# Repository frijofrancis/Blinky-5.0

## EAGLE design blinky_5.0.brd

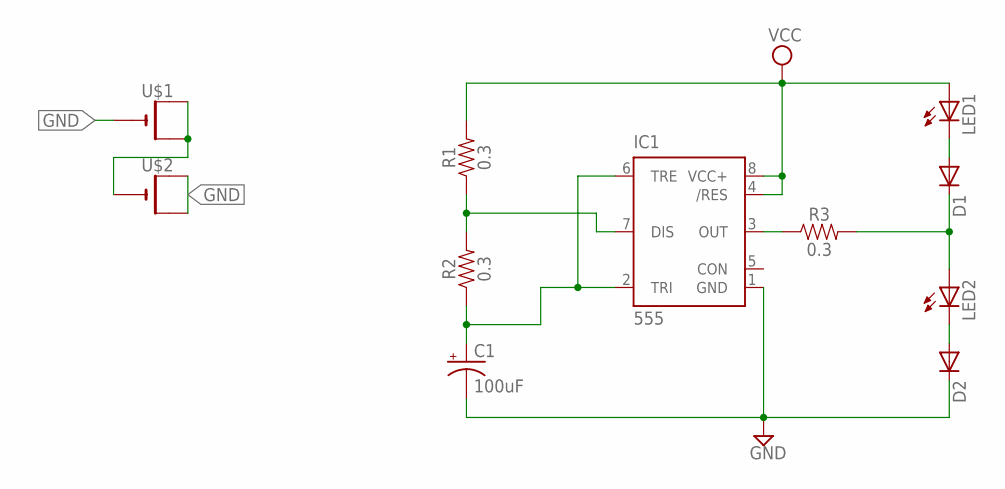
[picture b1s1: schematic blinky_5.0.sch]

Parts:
C1: 100uF; NIC_10X10.5_CAP
D1, D2: 1N4004; DO41-10
IC1: 555; SO08
LED1, LED2: LED5MM
R1, R2, R3: 0.3; 0805
U$1, U$2: CR1220SMT; CR1220-SMD

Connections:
GND: C1.-, D2.C, IC1.1 (GND), U$1.-, U$2.+$1 (+), U$2.+$2 (+1)
unnamed: IC1.7 (DIS), R1.1, R2.2
unnamed: C1.+, IC1.2 (TRI), IC1.6 (TRE), R2.1
unnamed: U$1.+$1 (+), U$1.+$2 (+1), U$2.-
unnamed: D2.A, LED2.K (C)
unnamed: D1.C, LED2.A, R3.2
unnamed: D1.A, LED1.K (C)
unnamed: IC1.3 (OUT), R3.1
VCC: IC1.4 (/RES), IC1.8 (VCC+), LED1.A, R1.2

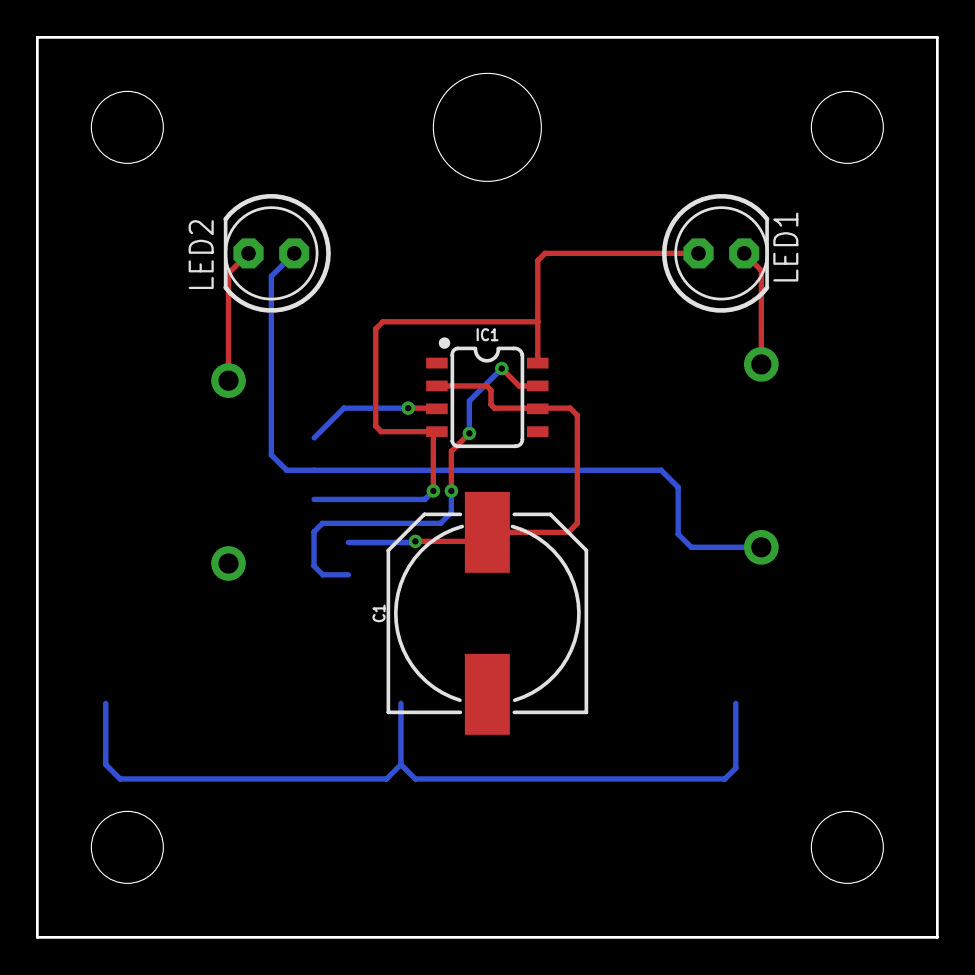
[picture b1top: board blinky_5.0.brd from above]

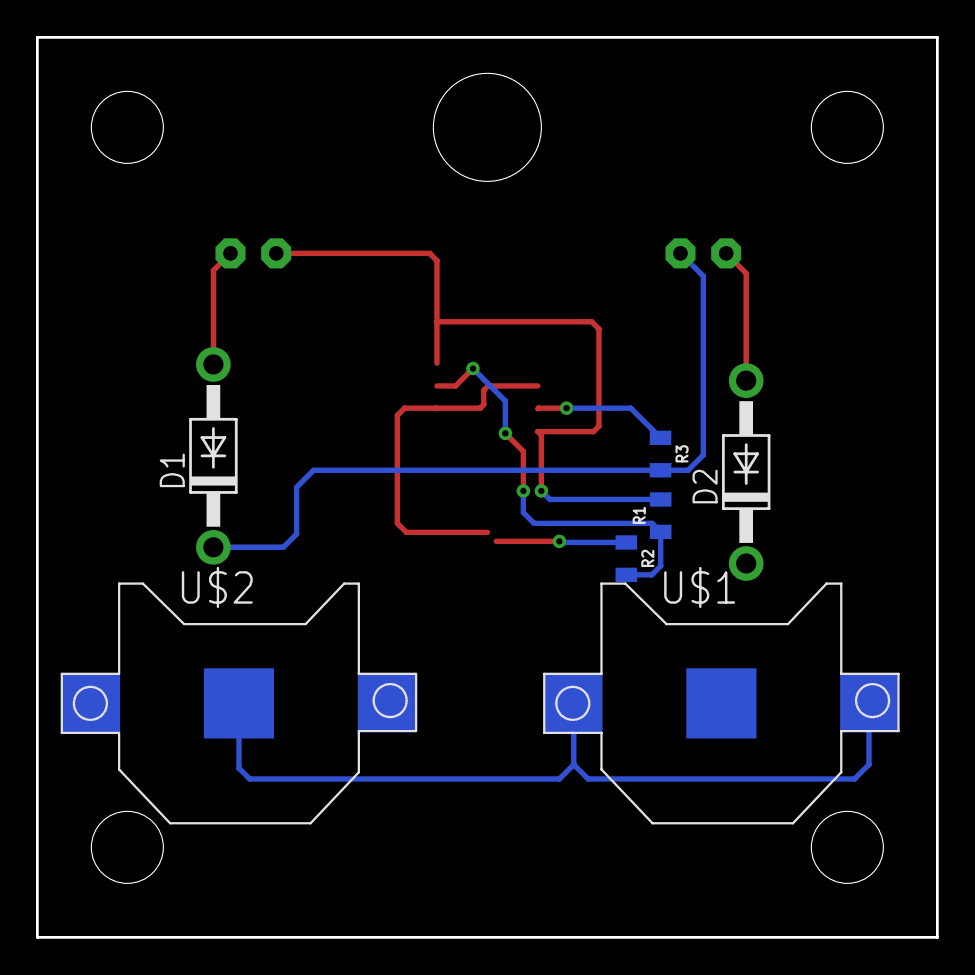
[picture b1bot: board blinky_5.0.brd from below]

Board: 2 copper layers, 50.0 x 50.0 mm, 11 parts (7 on the bottom side), 9 nets.

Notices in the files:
parts and their libraries:
SparkFun-Capacitors: Licensing: Creative Commons ShareAlike 4.0 International - https://creativecommons.org/licenses/by-sa/4.0
